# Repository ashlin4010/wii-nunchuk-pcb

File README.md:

# Wii Nunchuk PCB
A KiCad symbol and footprint for the Wii Nunchuk connector.

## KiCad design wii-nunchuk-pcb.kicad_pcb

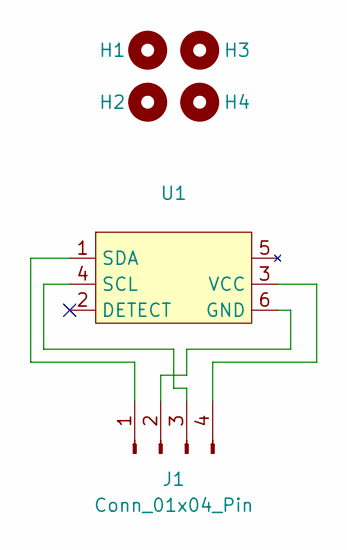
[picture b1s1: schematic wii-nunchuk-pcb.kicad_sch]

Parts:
H1, H2, H3, H4: MountingHole_2.2mm_M2
J1: Conn_01x04_Pin; PinHeader_1x04_P2.54mm_Vertical
U1: nunchuk

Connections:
unnamed: J1.1, U1.1 (SDA)
unnamed: J1.2, U1.6 (GND)
unnamed: J1.3, U1.4 (SCL)
unnamed: J1.4, U1.3 (VCC)

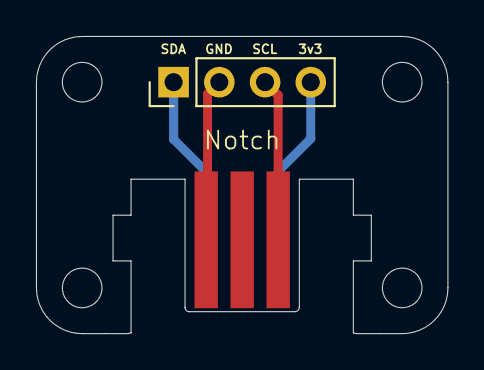
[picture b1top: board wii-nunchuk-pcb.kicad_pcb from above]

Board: 2 copper layers, 22.9 x 16.5 mm, 6 parts (0 on the bottom side), 4 nets.

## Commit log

2025-02-02 init
2025-02-12 Added new image
2025-02-12 Create LICENSE
